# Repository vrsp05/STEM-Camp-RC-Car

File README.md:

# BYU STEM Camp RC Car

## About This Project

Built by Victor Santana, Jaime Mejia, and Dan Barry as a proposed 2026 workshop for the BYU STEM Camp, this project delivers a robust, low-cost, and low-latency RC car framework. It transforms a standard ESP32-CAM into a standalone web server, video streamer, and motor controller, all without requiring an external internet connection. This interactive experience is designed to inspire students and provide hands-on learning in embedded systems, IoT technology, microcontrollers, and real-time wireless networking.

## Features

* **Low-Latency Video:** Optimized firmware utilizing CIF (400x296) resolution and an adjusted 10MHz clock speed for good MJPEG streaming over a local network.
* **WebSocket System:** Fast response times for driving controls and camera tuning, ensuring the car reacts to your steering instantly.
* **Frictionless Connectivity:** Auto-broadcasting, password-free Wi-Fi Access Points (e.g., `BYU-Car-1`). Students connect and drive instantly.
* **On-the-Fly Tuning:** A sleek, mobile-friendly web dashboard featuring a D-Pad and live sliders to control Headlight brightness, Camera Contrast, and Exposure.

## The Map (How is it organized?)

The repository is organized into four top-level folders to separate documentation, firmware, physical parts, and the web dashboard:

```text
STEM-CAMP-RC-CAR/
├── docs/              # user guides, lesson plans, and troubleshooting
├── firmware/          # ESP32/Arduino source code, configs, and builds
├── hardware/          # 3D-print STL, PCB files, schematics, and BOM
└── web_interface/     # dashboard UI (HTML/CSS/JS) and client assets
```

- **docs/**: Step‑by‑step manuals, programming guides, setup instructions, classroom materials, and troubleshooting notes to build and operate the car.
- **firmware/**: All source code and build artifacts for the ESP32 firmware (sketches, header/config files, build scripts, and CI files). Flashable binaries and board configuration live here.
- **hardware/**: CAD and STL files for 3D printing, PCB design and Gerber/board files, circuit schematics, wiring diagrams, and the bill of materials (BOM).
- **web_interface/**: The mobile‑friendly dashboard — HTML, CSS, JavaScript, assets, and client‑side WebSocket code used to view live video and control the car from a browser or phone.

## The Shopping List (Hardware Requirements)

To build this car, you will need a mix of custom parts and standard robotics electronics. Here is the detailed breakdown:

| Component | Quantity | Purchase Link |
| :--- | :--- | :--- |
| **ESP32-CAM (OV2640 camera)** | 1 | [DigiKey](https://www.digikey.com/short/w14d0qp4) |
| **DRV8833 Motor Controller** | 1 | [Amazon](https://a.co/d/00hcKW4g) |
| **8-Pin Female-to-Male Headers** | 2 | [DigiKey](https://www.digikey.com/short/5r3mm5rb) |
| **6-Pin Male-to-Male Headers** | 1 | [DigiKey](https://www.digikey.com/short/bth0dmv4) |
| **TT DC Gearbox Motors** | 4 | [Amazon](https://a.co/d/0djxPo1a) |
| **Rubber Wheels (for TT Motors)** | 4 | [Amazon](https://a.co/d/0djxPo1a) |
| **T-Brackets** | 4 | [/3d_prints/](hardware/3d_prints/T-Bracket_Mount.stl) |
| **Camera Mount** | 1 | [/3d_prints/](hardware/3d_prints/Camera_Mount.stl) |
| **Headlight Mount** | 1 | [/3d_prints/](/hardware/3d_prints/) |
| **6-32 x 1/4" Mounting Screws** | 8 | [Amazon](https://a.co/d/0eqBX8dm) |
| **Custom PCB Chassis** | 1 | [/electronics/](/hardware/electronics/RC_Car_PCB_v4.zip) |
| **4-AA Battery Holder** | 1 | [DigiKey](https://www.digikey.com/short/vzvpw4tr) |
| **Power Switch (SLW-1276864-4A-D)** | 1 | [DigiKey](https://www.digikey.com/short/3592nqjh) |
| **AA Batteries** | 4 | [Amazon](https://a.co/d/0iRKMYl3) |
| **Zip Tie** | 1 | [Amazon](https://a.co/d/0diwe9JH) |
| **Small Foam / Cardboard Rectangle** | 1 | [Amazon](https://a.co/d/09obGXU5) |

**Total estimated price:** $50-$80

## The Instructions (How do I build it?)

To build, program, and drive your car, you just need to download this repository and follow the step-by-step guides. You do not need to figure out how to build it from scratch, everything is already mapped out for you:

**Step 1: Download the Files (Fork and Clone)**

Before doing anything, you need to save a copy of all these project files to your own computer.

   * Click the **Fork** button at the top right of this GitHub page. This creates a safe copy in your own account so you can make changes without breaking the original project.
   * Open your computer's terminal and clone your new copy by typing:
      ```bash
      git clone https://github.com/vrsp05/STEM-Camp-RC-Car.git

      cd STEM-Camp-RC-Car
      ```

**Step 2: Set Up Your Computer**

   * **File:** [environment_setup.md](/docs/environment/environment_setup.md)
   * **What it does:** This guide shows you exactly how to install the Arduino IDE on your computer, add the ESP32 chip definitions, and make sure your computer can talk to the car's brain over a USB cable.

**Step 3: Assemble the Hardware**

   * **File:** [assembly_guide.pdf](/docs/assembly_docs/assembly_guide.pdf)
   * **What it does:** This is your physical instruction manual. It has clear pictures and step-by-step directions showing you how to solder the electronics to the custom PCB chassis, mount the four yellow gearbox motors using your screws, and attach the wheels.

**Step 4: Program the Brain**

   * **File:** [programming_guide.md](/docs/programming/programming_instructions.md)
   * **What it does:** This guide teaches you how to open the code, give your car a unique Wi-Fi network name, and safely flash the firmware onto the ESP32-CAM using the correct settings so it is ready to drive.

## Credits

**Hardware & Custom PCB Design:**
- **Dan Barry** and **Jaime Mejia** for engineering the custom PCB and assembling the physical hardware of the car.

**Software & Inspiration:**
This project builds upon excellent educational resources from the community:
- [ESP32-CAM Streaming with Motor Control](https://www.youtube.com/watch?v=7I4SnUXxUR0&t=2s) by Jeevan Jee
- [Simple Circuits Tutorial](https://www.youtube.com/watch?v=Du1UvHnD-ZM) by Simple Circuits
- [ESP32-CAM Car Robot Web Server](https://randomnerdtutorials.com/esp32-cam-car-robot-web-server/) by Random Nerd Tutorials
- [RoboArmy Project](https://youtu.be/YqQc_Sm9vlA) by RoboArmy

---

Developed for the BYU STEM Camp (2026).

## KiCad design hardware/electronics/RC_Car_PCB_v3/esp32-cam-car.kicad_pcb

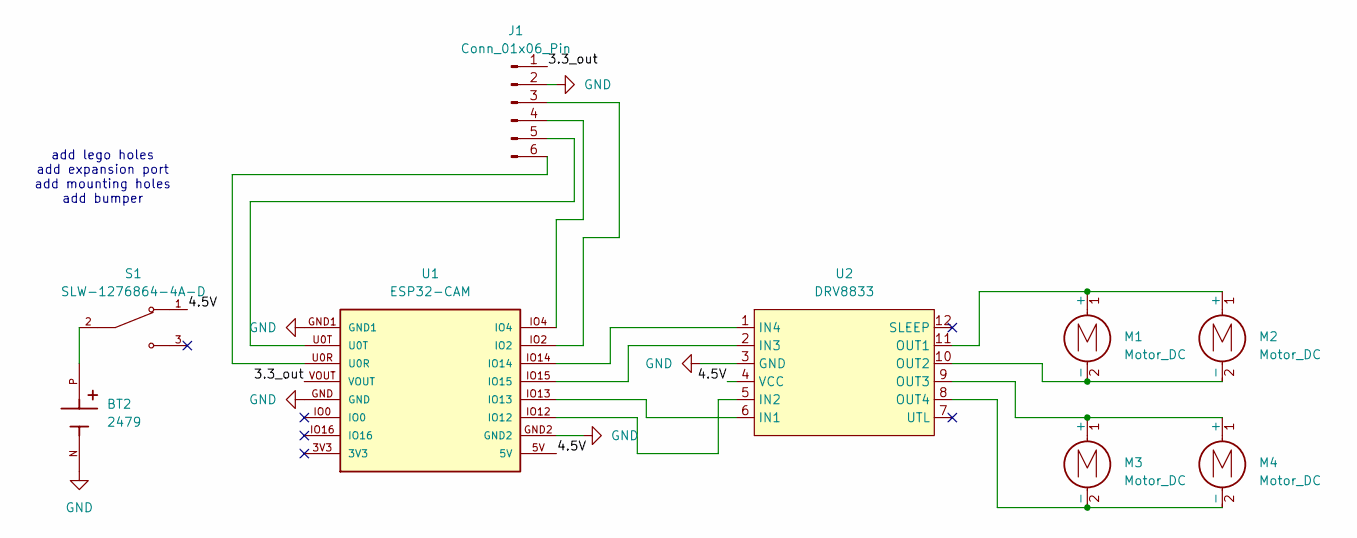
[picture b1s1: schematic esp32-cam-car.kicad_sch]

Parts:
BT2: 2479; BAT_2479; PARTREV E
J1: Conn_01x06_Pin; PinSocket_1x06_P2.54mm_Vertical
M1, M2, M3, M4: Motor_DC; SolderWire-0.127sqmm_1x02_P3.7mm_D0.48mm_OD1mm_Relief2x
S1: SLW-1276864-4A-D; SW_SLW-1276864-4A-D; PARTREV 1.01
U1: ESP32-CAM
U2: DRV8833; DIP-12_W10.16mm_LongPads

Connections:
/3.3_out: J1.1, U1.VOUT
/4.5V: S1.1, U1.5V, U2.4 (VCC)
GND: BT2.N, J1.2, U1.GND, U1.GND1, U1.GND2, U2.3 (GND)
unnamed: BT2.P, S1.2
unnamed: J1.3, U1.IO2
unnamed: J1.4, U1.IO4
unnamed: J1.5, U1.U0T
unnamed: J1.6, U1.U0R
unnamed: M1.1 (+), M2.1 (+), U2.11 (OUT1)
unnamed: M1.2 (-), M2.2 (-), U2.10 (OUT2)
unnamed: M3.1 (+), M4.1 (+), U2.9 (OUT3)
unnamed: M3.2 (-), M4.2 (-), U2.8 (OUT4)
unnamed: U1.IO13, U2.6 (IN1)
unnamed: U1.IO12, U2.5 (IN2)
unnamed: U1.IO15, U2.2 (IN3)
unnamed: U1.IO14, U2.1 (IN4)

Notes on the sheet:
add lego holes add expansion port add mounting holes add bumper

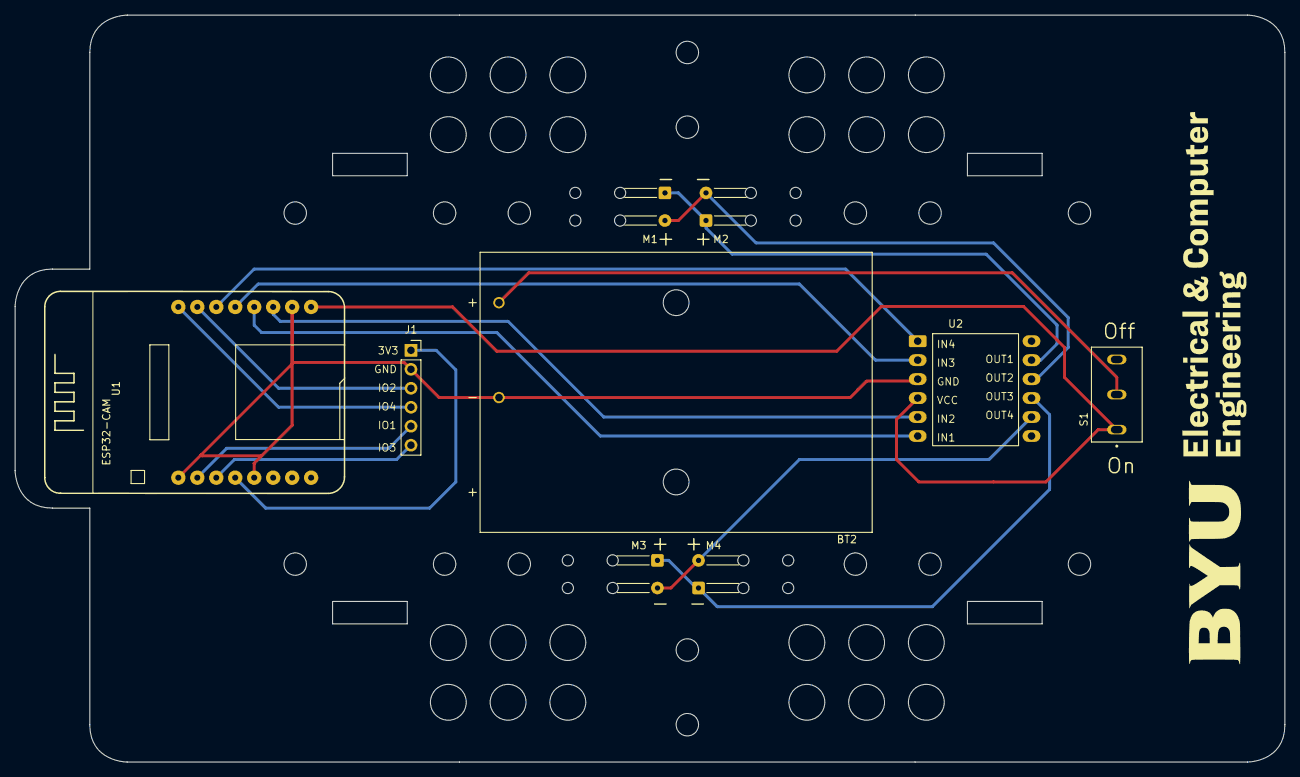
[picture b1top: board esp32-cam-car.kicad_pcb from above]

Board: 2 copper layers, 170.0 x 100.0 mm, 9 parts (0 on the bottom side), 16 nets.

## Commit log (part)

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2026-05-18 Created repo and hardware test file to test ESP32 CAM MB
2026-05-19 finished esp32 testing and created first website verstion.
    esp32 is working good. website is still not connected to live stream.
2026-05-19 website is working okey now.
    created proxy_server, separated html, css, and js code.
2026-05-20 created test/beta and official website. also updated website styling to be more BYU brand
2026-05-20 Added BYU logo and fixed typos
2026-05-20 Meged both sites. Compacted site, and fixed logo
2026-05-20 Successfully made the ESP32 its own router
2026-05-20 Made ESP32 its own wifi router and hosted its own website.
2026-05-20 Deleted BYU logo
    No longer needed.
2026-05-21 Upgraded website.
    Added car controls, improved site, and improved communication between esp32 and device
2026-05-21 Upgraded website controls
    Included controls for brightness, contrast, and the LED (or headlights).
2026-05-21 Created setup page.
    People can now name their car's wifi and setup their own password.
2026-05-22 Updated setup process.
    Added a redirect to the setup page if custome wifi name and passwords are not created yet.
2026-05-22 Delete setup.h
    We no longer need the setup rout
2026-05-23 Removed setup page, no longer needed.
2026-05-23 Updated readme file
2026-05-23 Proxy file no longer needed. Updated readme
2026-05-24 Updated README, ADDED libraries instructions, created a issues documentation
2026-05-27 Updated camera resolution, updated max LED brightness, and added a BOOT FLASH
2026-05-27 Updated Brightness cap and flash intensity
2026-05-28 Stop tracking Issues_Documentation.md
2026-05-28 Updated the README
2026-05-28 added and updated the student guide
2026-06-05 Updated the motor control login and added pic schematic
2026-06-05 updated comments
2026-06-09 Added code to test a single motor
2026-06-09 updated motor control logic
2026-06-11 updated driving software
2026-06-11 updated documentation
2026-06-17 updated the readme doc
    updated the documentation of the project
2026-06-17 moved test files
2026-06-17 updated documentation once more
2026-06-17 updated the index.html to be website sandbox
2026-06-22 updated folder structure and added assemply guide text file (this is just raw text)
2026-06-24 Added assembly guide (completed) and 3d printed files
2026-06-29 updating main code by cleaning, adding clearer features, and fixing comments, moved also schematic and create a copy of last working ino file
2026-06-29 Added feature to allow just one connection per car
2026-06-29 updated website to show error if another person attempts to connect when there is a connection stablished already
2026-06-29 Rearranged files order and renamed
2026-06-29 updated the naming of files.
2026-06-30 working on updating the documentation
